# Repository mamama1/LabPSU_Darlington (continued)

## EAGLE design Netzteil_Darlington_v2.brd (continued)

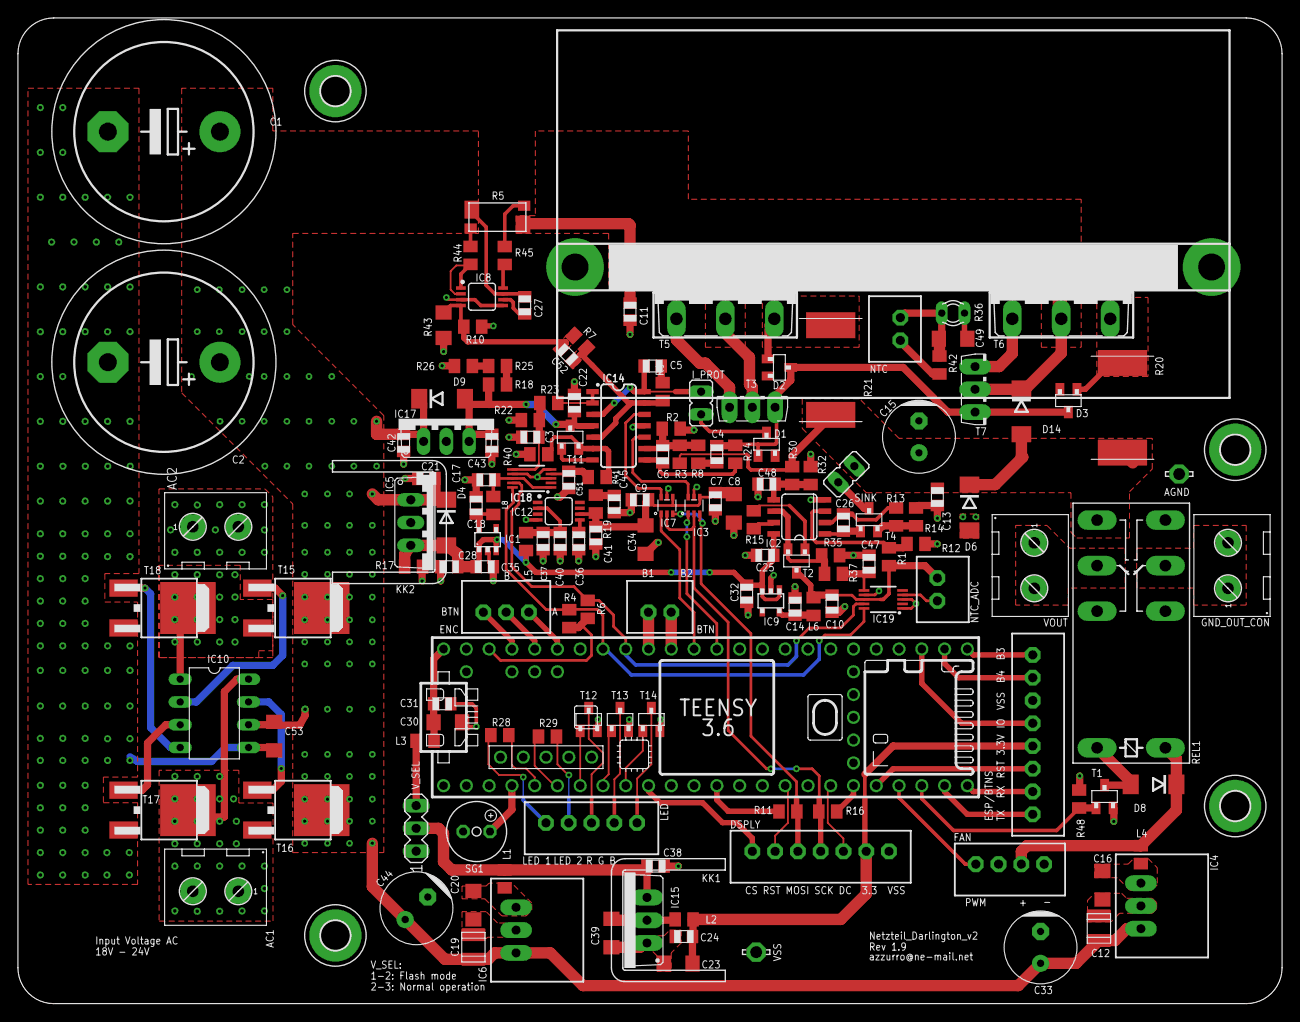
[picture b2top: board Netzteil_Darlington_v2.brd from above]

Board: 2 copper layers, 141.0 x 109.9 mm, 163 parts (0 on the bottom side), 109 nets.

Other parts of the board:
KK2: D01S
LED: JST-PH-2.0-5P
NTC: JST-PH-2.0-2P
NTC_ADC: JST-PH-2.0-2P
R15: 1k5 5% 1/8W; C0805K

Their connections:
3.3V_TH: NTC.2; also elsewhere on the board
unnamed 49: LED.3; also elsewhere on the board
unnamed 60: LED.1; also elsewhere on the board
unnamed 63: LED.2; also elsewhere on the board
unnamed 80: LED.4; also elsewhere on the board
unnamed 82: LED.5; also elsewhere on the board
TH0: NTC.1; also elsewhere on the board
TH0_ADC: NTC_ADC.1; also elsewhere on the board

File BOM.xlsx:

Qty | Value | Device | Package | Parts | Description | OC_MOUSER | OC_MOUSER_ADD | OC_MOUSER_ADD2
2 |  | JP1E | JP1 | I_PROT, SINK | JUMPER
3 |  | JST-PH-2.0-2P | JST-PH-2.0-2P | BTN, NTC, NTC_ADC | PIN HEADER
1 |  | JST-PH-2.0-3P | JST-PH-2.0-3P | ENC | PIN HEADER
1 |  | JST-PH-2.0-4P | JST-PH-2.0-4P | FAN | PIN HEADER
1 |  | JST-PH-2.0-5P | JST-PH-2.0-5P | LED | PIN HEADER
1 |  | JST-PH-2.0-7P | JST-PH-2.0-7P | DSPLY | PIN HEADER
1 |  | JST-PH-2.0-8P | JST-PH-2.0-8P | ESP/BTNS | PIN HEADER
1 |  | KL2691311500002 | KL2-691311500002 | VOUT | Printklemme 2-polig | 710-691311500002 | 565-72912-2 | 565-6883
1 |  | MA03-1 | MA03-1 | V_SEL | PIN HEADER
2 | 0R1 0.5% 7W | R-SMDSLN2 | SLN2 | R20, R21 | R | 66-SLN5TTED82L0D
1 | 1.27R 1% 1/10W | R-SMD0805 | C0805K | R19 | R | 71-CRCW08051R27FKEA
2 | 10.1k 0.1% 10ppm 1/10W | R-SMD0805 | C0805K | R22, R32 | R | 660-RN732ATTD1012B25
2 | 10000µ/50V | CPOL-USE10-22.5 | EB22,5D | C1, C2 | POLARIZED CAPACITOR, American symbol | 647-UVZ1H103MRD
2 | 100R 0.1% 5ppm 1/10W | R-SMD0805 | C0805K | R44, R45 | R | 756-PCF080513100RBT1
1 | 100k | NTC640 | P640 | R36 | PHILIPS NTC | 594-NTCLE213E3104HXB
1 | 100n opt/50V | CC/0805 | 805 | C13 | Kondensator | 810-C2012X7R2A104K
9 | 100n/16V | CC/0805 | 805 | C3, C7, C9, C10, C17, C24, C31, C38, C48 | Kondensator | 810-C2012X7R2A104K
5 | 100n/35V | CC/0805 | 805 | C22, C25, C28, C40, C43 | Kondensator | 810-C2012X7R2A104K
1 | 100n/50V | CC/0805 | 805 | C27 | Kondensator | 810-C2012X7R2A104K
3 | 100µ/50V | C+3.5/8 | C+/3.5/8 | C15, C33, C44 |  | 667-EEU-FR1H101
1 | 10R 0.5% 50 ppm 1/4W | R-SMD0805 | C0805K | R14 | R | 660-SG73G2ATTD10R0D
1 | 10k 0.1% 10ppm | R-SMD0805 | C0805K | R2 | R | 667-ERA-6ARW103V
4 | 10k 5% 1/10W | R-SMD0805 | C0805K | R4, R6, R7, R48 | R | 652-CR0805-JW-103ELF
1 | 10m 0.1% 15ppm 0.5W | R-CSM2512 | CSM2512 | R5 |  | 71-CSM25120R0100BST
2 | 10n/16V | CC/0805 | 805 | C47, C51 | Kondensator | 80-C0805C103K1R
1 | 10n/50V | CC/0805 | 805 | C4 | Kondensator | 80-C0805C103K1R
7 | 10µ/16V | CC/1206 | 1206 | C8, C20, C23, C30, C34, C39, C49 | Kondensator | 963-TMK316AB7106KL-T
1 | 10µ/25V | CC/1206 | 1206 | C16 | Kondensator | 963-TMK316AB7106KL-T
2 | 10µ/50V | CAPACITOR-1210 | C1210 | C12, C19 | Capacitors | 81-GRM32ER71H106MA2L
1 | 12k 0.5% 50 ppm 1/10W | R-SMD0805 | C0805K | R1 | R | 754-RR1220P-123D
1 | 1k 0.5% 50 ppm 1/10W | R-SMD0805 | C0805K | R13 | R | 754-RR1220P-102D
4 | 1k 1% 1/8W | R-SMD0805 | C0805K | R18, R24, R25, R26 | R | 652-CR0805FX-1001ELF
1 | 1k5 5% 1/8W | R-SMD0805 | C0805K | R15 | R | 652-CR0805FX-1501ELF
2 | 1n/50V | CC/0805 | 805 | C5, C26 | Kondensator | 603-CC805KRX7R0BB102
5 | 1µ/16V | CC/0805 | 805 | C14, C18, C36, C41, C45 | Kondensator | 963-UMK212B7105KG-T
3 | 1µ/35V | CC/0805 | 805 | C32, C35, C37 | Kondensator | 963-UMK212B7105KG-T
1 | 1µ/50V | CC/1206 | 1206 | C53 | Kondensator | 603-CC126KKX7R9BB105
2 | 2.2k 5% 1/10W | R-SMD0805 | C0805K | R37, R41 | R | 652-CR0805FX-2201ELF
2 | 220R 5% 1/10W | R-SMD0805 | C0805K | R28, R29 | R | 652-CR0805FX-2200ELF
1 | 221R 0.5% 50ppm 1/10W | R-SMD0805 | C0805K | R12 | R | 754-RR1220P-2210D-M
2 | 22R 5% 1/10W | R-SMD0805 | C0805K | R11, R16 | R | 652-CR0805JW-220ELF
1 | 22p opt/35V C0G | CC/0805 | 805 | C52 | Kondensator | 603-CC805JRNPO9BN220
1 | 22pF/35V C0G | CC/0805 | 805 | C6 | Kondensator | 603-CC805JRNPO9BN220
1 | 2k2 5% 1/8W | R-SMD0805 | C0805K | R17 | R | 652-CR0805JW-222ELF
1 | 30k 0.1% 10ppm | R-SMD0805 | C0805K | R3 | R | 667-ERA-6ARW303V
1 | 330n opt/50V | CC/0805 | 805 | C11 | Kondensator | 80-C0805C334K5RECTU
2 | 330n/50V | CC/0805 | 805 | C21, C42 | Kondensator | 80-C0805C334K5RECTU
1 | 4.7k 1% 1/10W | R-SMD0805 | C0805K | R9 | R | 652-CR0805FX-4701ELF
2 | 4.7k 5% 1/10W | R-SMD0805 | C0805K | R35, R40 | R | 652-CR0805FX-4701ELF
1 | 4.7k opt 1% 1/10W | R-SMD0805 | C0805K | R10 | R | 652-CR0805FX-4701ELF
1 | 47k 1% 1/10W | R-SMD0805 | C0805K | R8 | R | 652-CR0805FX-4702ELF
1 | 5k 0.1% 25ppm | R-EU_R1206 | R1206 | R43 | RESISTOR, European symbol | 71-TNPW12065K00BEEN
1 | 64.9k 1% 1/10W | R-SMD0805 | C0805K | R42 | R | 652-CR0805FX-6492ELF
1 | 7815TV | 7815TV | TO220V | IC5 | Positive VOLTAGE REGULATOR | 511-L7815CV-DG
1 | 7818TV | 7818TV | TO220V | IC17 | Positive VOLTAGE REGULATOR | 511-L7818CV-DG
2 | 90.9k 0.1% 10ppm 1/10W | R-SMD0805 | C0805K | R23, R30 | R | 279-RN73CA-90.9K
1 | AC1 | KL2691311500002 | KL2-691311500002 | AC1 | Printklemme 2-polig | 710-691311500002 | 693-8601.2001.08 | 693-3101.0010
1 | AC2 | KL2691311500002 | KL2-691311500002 | AC2 | Printklemme 2-polig | 710-691311500002 | 693-8601.2001.08
2 | ADS1115 | ADS1015 | MSOP10 | IC18, IC19 | ADS1015 12-BIT ADC | 595-ADS1115IDGSR
3 | BAT54FILMY | DBAT54FILMY | SOT23 | D1, D2, D3 |  | 511-BAT54FILMY
2 | BC847ALT1G | T-NPNSOT23-BEC | SOT23-BEC | T2, T11 | NPN Transistor | 863-BC847ALT1G
2 | BD139 | T-NPNTO126-ECB | TO126 | T3, T7 | NPN Transistor | 511-BD139-10
1 | BUZZER | BUZZER | 254-EMB73-RO | SG1 | BUZZER Source: Buerklin | 254-EMB73-RO
5 | CGRB307-G | DWIDE | DO214AA-CGRB307-G | D4, D6, D8, D9, D14 |  | 750-CGRB307-G
1 | D01S | D01S | D01S | KK1 | HEATSINK
2 | DAC8311 | DAC8X11 | SC-70-6 | IC3, IC7 |  | 595-DAC8311IDCKR
1 | G2R-2-DC12 | REL-2UG2R2 | REL-G2R2 | REL1 |  | 653-G2R-2-DC12
1 | GND | KL2691311500002 | KL2-691311500002 | GND_OUT_CON | Printklemme 2-polig | 710-691311500002
1 | HSOMNI-UNI-41-75 | HSOMNI-UNI-41-75 | OMNI-UNI-41-75 | HS2 |  | 567-OMNI-UNI-41-75 | 567-OMNI-UC | 567-CD-02-05-247
4 | IRFR7546TRPBF | T-NMOSNTD4963N | DPACK | T15, T16, T17, T18 | Transistor N-Channel MOSFET | 942-IRFR7546TRPBF
1 | LD33V | LD33V | TO220V | IC15 |  | 511-LD1117V33
2 | LSP13 | LSP13 | LSP13 | AGND, VSS | SOLDER PAD drill 1.3 mm, distributor Buerklin, 12H562
1 | LT4320DIL08 | LT4320DIL08 | DIL08 | IC10 |  | 584-LT4320HN8-1#PBF
1 | LTC6102HMS8#PBF | LTC6102 | MSOP8-0.65-3X3MM | IC8 |  | 584-LTC6102HMS8#PBF
4 | MOUNT-PAD-ROUND3.3 | MOUNT-PAD-ROUND3.3 | 3,3-PAD | H1, H2, H3, H4 | MOUNTING PAD, round
7 | MPZ2012S601AT000 | L0805 | C0805K | L1, L2, L3, L4, L5, L6, L8 | High Power Density, High Efficiency, Shielded Inductors | 810-MPZ2012S601AT000
2 | NCP718BSN330T1G | NCP718 | SOT23-5 | IC1, IC9 |  | 863-NCP718BSN330T1G
1 | OPA2197 | DUAL-OPVSOP8 | SOP8 | IC2 |  | 595-OPA2197IDR
5 | PMV130ENEAR | T-NMOSIRLML2502PBF | SOT23 | T1, T4, T12, T13, T14 | Transistor N-Channel MOSFET | 771-PMV130ENEAR
1 | QUAD-OPVOPA4197 | QUAD-OPVOPA4197 | SO14 | IC14 |  | 595-OPA4197IDR
1 | REF5040 | REF50XXVSSOP8 | MSOP8-0.65-3X3MM | IC12 |  | 595-REF5040AIDGKR
1 | TEENSY_3.5/3.6 | TEENSY_3.5/3.6 | TEENSY_3.5/3.6 | U$33 |  | 474-DEV-14055
2 | TIP3055 | T-NPNTOP3AV-BCE | TOP3AV | T5, T6 | NPN Transistor | 863-TIP3055G
1 | VXO78012-1000 | 78XX-DC-DC-UNI-VXO-OKI | 78XX-DC-DC | IC4 |  | 490-VXO7812-1000
1 | VXO7805-1000 | 78XX-DC-DC-UNI-VXO-OKI | 78XX-DC-DC | IC6 |  | 490-VXO7805-1000

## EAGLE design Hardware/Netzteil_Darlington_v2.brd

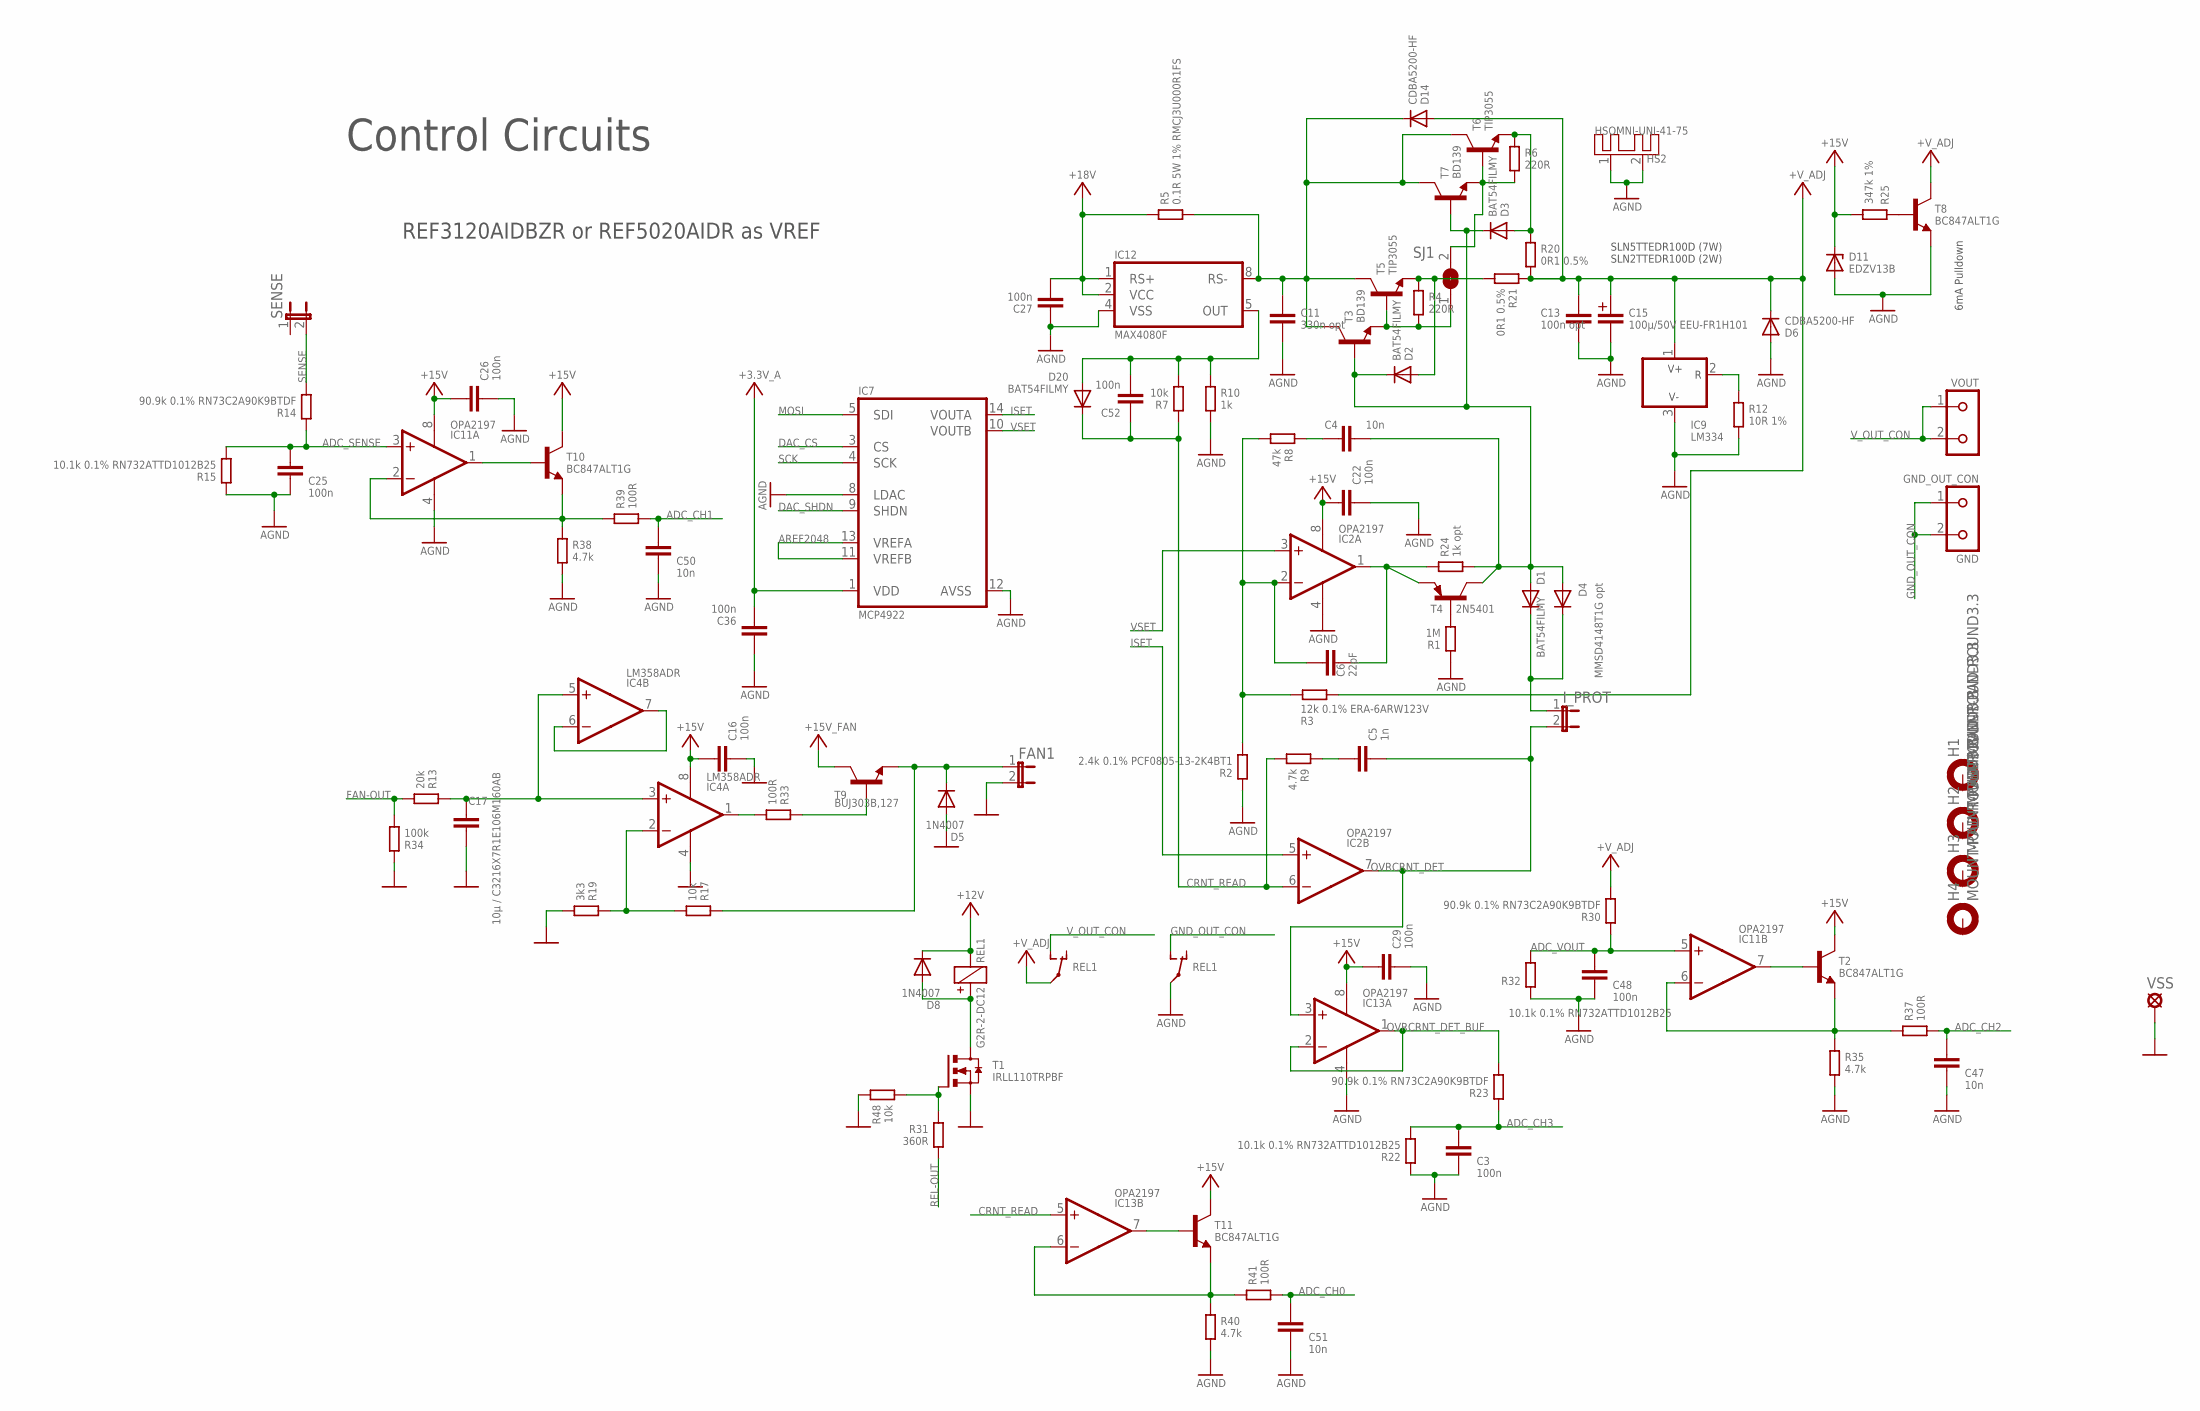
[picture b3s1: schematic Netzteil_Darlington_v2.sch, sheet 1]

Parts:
C3, C16, C22, C25, C26, C27, C29, C36, C48, C52: 100n; 0805
C4, C47, C50, C51: 10n; 0805
C5: 1n; 0805
C6: 22pF; 0805
C11: 330n opt; 0805
C13: 100n opt; 0805
C15: 100µ/50V EEU-FR1H101; C+/3.5/8
C17: 10µ / C3216X7R1E106M160AB; 1206
D1, D2, D3, D20: BAT54FILMY; SOT23
D4: MMSD4148T1G opt; SOD-123
D5, D8: 1N4007; DO214AA
D6, D14: CDBA5200-HF; DO214AC-2
D11: EDZV13B; SOD-523
FAN1: JP1E; JP1
GND_OUT_CON: GND; KL2-691311500002
H1, H2, H3, H4: MOUNT-PAD-ROUND3.3; 3,3-PAD
HS2: HSOMNI-UNI-41-75; OMNI-UNI-41-75
IC2, IC11, IC13: OPA2197; SOP8
IC4: LM358ADR; SOP8
IC7: MCP4922; TSSOP14
IC9: LM334; TO92-G
IC12: MAX4080F; SOP8
I_PROT: JP1E; JP1
R1: 1M; C0603K
R2: 2.4k 0.1% PCF0805-13-2K4BT1; C0805K
R3: 12k 0.1% ERA-6ARW123V; C0805K
R4, R6: 220R; C0805K
R5: 0.1R 5W 1% RMCJ3U000R1FS; RMC-J3
R7, R17, R48: 10k; C0805K
R8: 47k; C0805K
R9, R35, R38, R40: 4.7k; C0805K
R10: 1k; C0805K
R12: 10R 1%; C0805K
R13: 20k; C0805K
R14, R23, R30: 90.9k 0.1% RN73C2A90K9BTDF; C0805K
R15, R22, R32: 10.1k 0.1% RN732ATTD1012B25; C0805K
R19: 3k3; C0805K
R20, R21: 0R1 0.5%; SLN2
R24: 1k opt; C0805K
R25: 347k 1%; C0805K
R31: 360R; C0805K
R33, R37, R39, R41: 100R; C0805K
R34: 100k; C0805K
REL1: G2R-2-DC12; REL-G2R2
SENSE: JP1E; JP1
SJ1: SJ
T1: IRLL110TRPBF; SOT223-4
T2, T8, T10, T11: BC847ALT1G; SOT23-BEC
T3, T7: BD139; TO126
T4: 2N5401; TO92-G
T5, T6: TIP3055; TOP3AV
T9: BUJ303B,127; TO220V
VOUT: KL2691311500002; KL2-691311500002
VSS: LSP13

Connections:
+3.3V_A: C36.2, IC7.1 (VDD); also elsewhere on the board
+12V: D8.C, REL1.-; also elsewhere on the board
+15V: C16.1, C22.1, C26.1, C29.1, D11.C, IC2.8 (V+), IC4.8 (V+), IC11.8 (V+), IC13.8 (V+), R25.2, T2.C, T10.C, T11.C; also elsewhere on the board
+15V_FAN: T9.2 (C); also elsewhere on the board
+18V: C27.2, IC12.1 (RS+), IC12.2 (VCC), R5.1; also elsewhere on the board
+V_ADJ: C13.1, C15.+, D6.C, D14.A, IC9.1 (V+), R3.1, R20.2, R21.1, R30.2, REL1.P1, T8.C
ADC_CH0: C51.1, R41.2; also elsewhere on the board
ADC_CH1: C50.1, R39.2; also elsewhere on the board
ADC_CH2: C47.1, R37.2; also elsewhere on the board
ADC_CH3: C3.1, R22.2, R23.1; also elsewhere on the board
ADC_SENSE: C25.1, IC11.3 (+IN), R14.1, R15.2
ADC_VOUT: C48.1, IC11.5 (+IN), R30.1, R32.2
AGND: C3.2, C11.2, C13.2, C15.-, C22.2, C25.2, C26.2, C27.1, C29.2, C36.1, C47.2, C48.2, C50.2, C51.2, D6.A, D11.A, HS2.1, HS2.2, IC2.4 (V-), IC7.8 (LDAC), IC7.12 (AVSS), IC9.3 (V-), IC11.4 (V-), IC12.4 (VSS), IC13.4 (V-), R1.1, R2.1, R10.2, R12.2, R15.1, R22.1, R32.1, R35.2, R38.2, R40.2, REL1.P2, T8.E; also elsewhere on the board
AREF2048: IC7.11 (VREFB), IC7.13 (VREFA); also elsewhere on the board
CRNT_READ: C52.1, D20.3 (C), IC2.6 (-IN), IC13.5 (+IN), R7.1, R9.2
DAC_CS: IC7.3 (CS); also elsewhere on the board
DAC_SHDN: IC7.9 (SHDN); also elsewhere on the board
FAN-OUT: R13.2, R34.2; also elsewhere on the board
GND_OUT_CON: GND_OUT_CON.1, GND_OUT_CON.2, REL1.S2 (S)
ISET: IC2.5 (+IN), IC7.14 (VOUTA)
MOSI: IC7.5 (SDI); also elsewhere on the board
unnamed: C11.1, D14.C, IC12.8 (RS-), R5.2, T3.2 (C), T5.C, T6.C, T7.2 (C)
unnamed: D3.1 (A), R6.1, R20.1, T6.E
unnamed: R6.2, SJ1.2, T6.B, T7.1 (E)
unnamed: C6.1, IC2.2 (-IN), R2.2, R3.2, R8.2
unnamed: C52.2, D20.1 (A), IC12.5 (OUT), R7.2, R10.1
unnamed: D2.1 (A), R4.1, R21.2, T5.E
unnamed: D1.3 (C), D4.C, I_PROT.1
unnamed: R25.1, T8.B
unnamed: D8.A, REL1.+, T1.2 (D), T1.4 (D)
unnamed: R4.2, SJ1.1, T3.1 (E), T5.B
unnamed: IC9.2 (R), R12.1
unnamed: IC4.6 (-IN), IC4.7 (OUT)
unnamed: R1.2, T4.2 (B)
unnamed: C6.2, IC2.1 (OUT), R24.1, T4.1 (E)
unnamed: C4.2, D1.1 (A), D2.3 (C), D3.3 (C), D4.A, R24.2, T3.3 (B), T4.3 (C), T7.3 (B)
unnamed: C4.1, R8.1
unnamed: C5.1, R9.1
unnamed: C17.2, IC4.3 (+IN), IC4.5 (+IN), R13.1
unnamed: D5.C, FAN1.1, R17.1, T9.3 (E)
unnamed: IC4.2 (-IN), R17.2, R19.1
unnamed: R33.1, T9.1 (B)
unnamed: IC4.1 (OUT), R33.2
unnamed: R31.1, R48.2, T1.1 (G)
unnamed: IC11.7 (OUT), T2.B
unnamed: IC11.6 (-IN), R35.1, R37.1, T2.E
unnamed: IC11.1 (OUT), T10.B
unnamed: IC11.2 (-IN), R38.1, R39.1, T10.E
unnamed: IC13.7 (OUT), T11.B
unnamed: IC13.6 (-IN), R40.1, R41.1, T11.E
OVRCRNT_DET: C5.2, IC2.7 (OUT), IC13.3 (+IN), I_PROT.2
OVRCRNT_DET_BUF: IC13.1 (OUT), IC13.2 (-IN), R23.2
REL-OUT: R31.2; also elsewhere on the board
SCK: IC7.4 (SCK); also elsewhere on the board
SENSE: R14.2, SENSE.2
VSET: IC2.3 (+IN), IC7.10 (VOUTB)
VSS: C16.2, C17.1, D5.A, FAN1.2, IC4.4 (V-), R19.2, R34.1, R48.1, T1.3 (S), VSS.MP; also elsewhere on the board
V_OUT_CON: REL1.S1 (S), VOUT.1, VOUT.2

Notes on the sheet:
Control Circuits
6mA Pulldown
SLN5TTEDR100D (7W) SLN2TTEDR100D (2W)
REF3120AIDBZR or REF5020AIDR as VREF

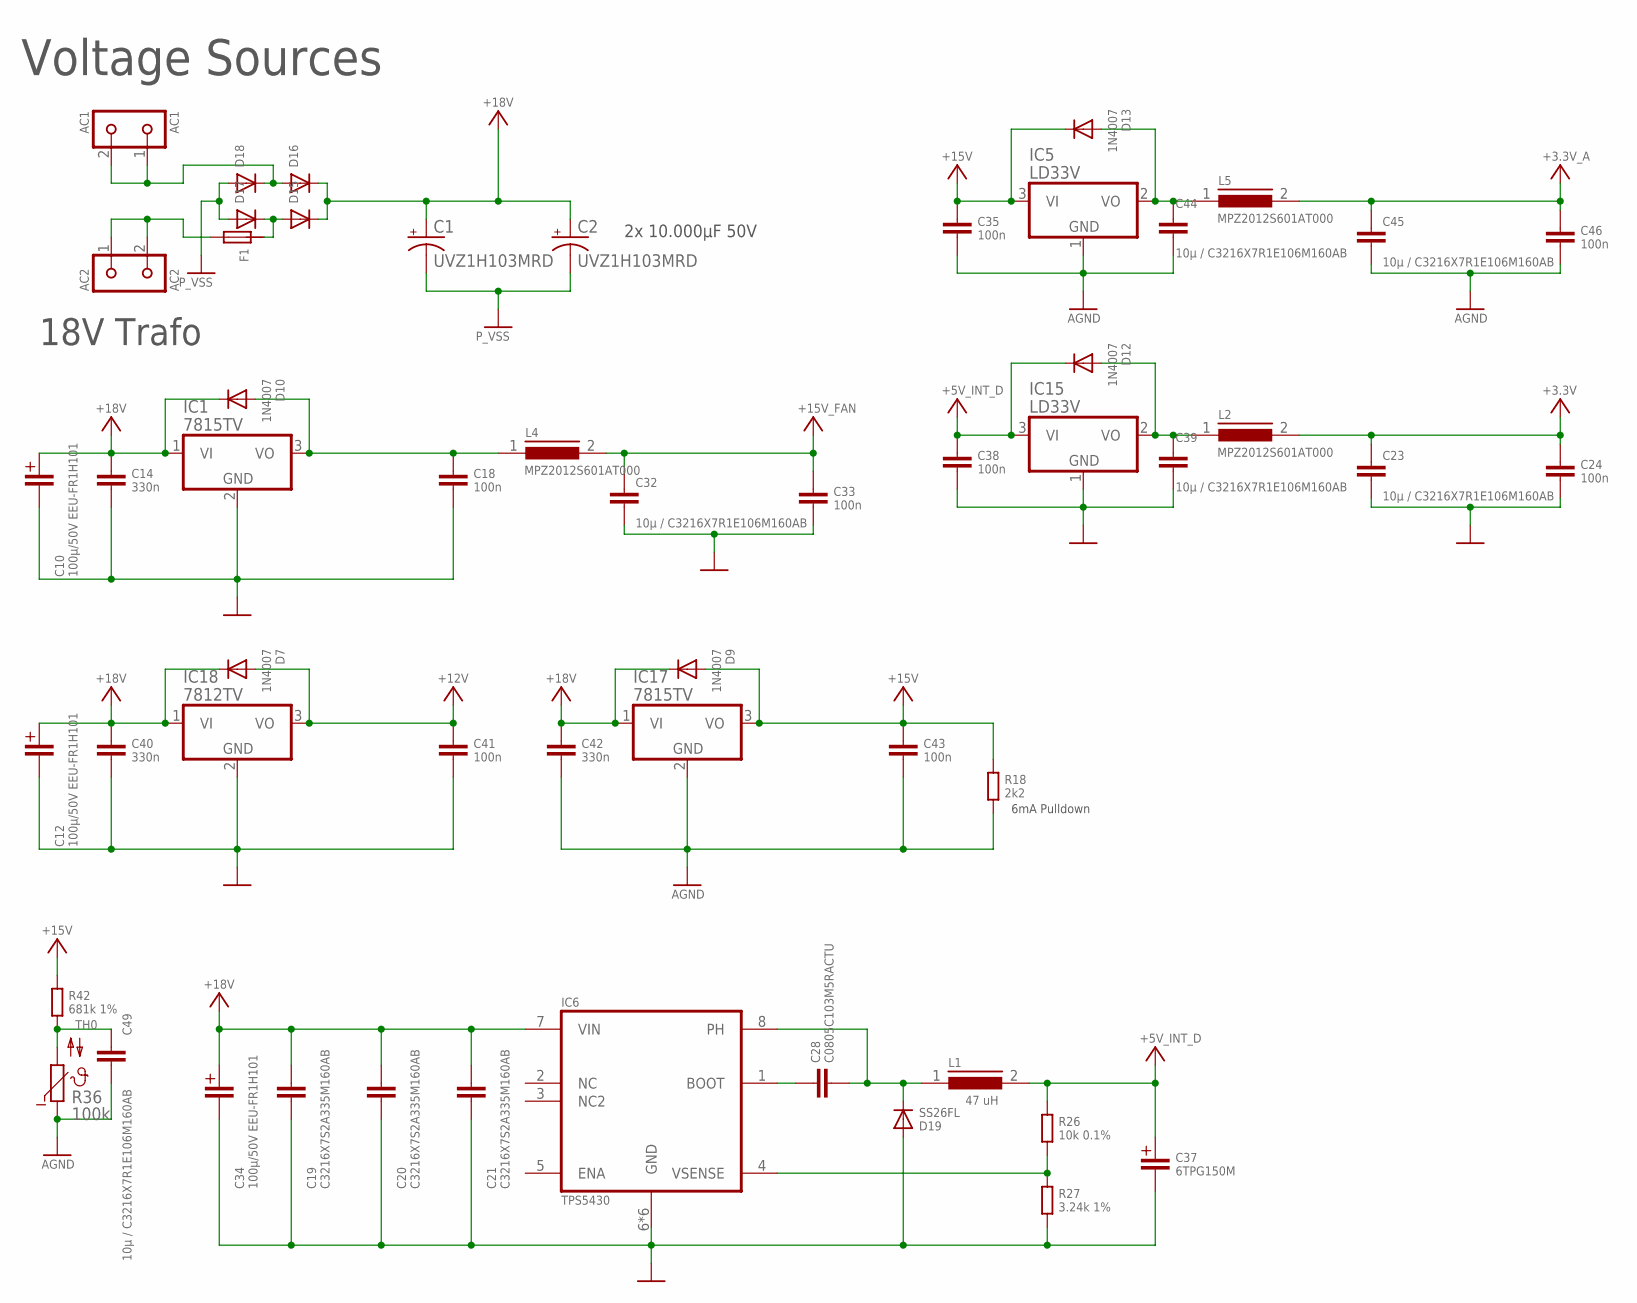
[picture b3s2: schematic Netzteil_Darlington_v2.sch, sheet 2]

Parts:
AC1: AC1; KL2-691311500002
AC2: AC2; KL2-691311500002
C1, C2: UVZ1H103MRD; EB22,5D
C10, C12, C34: 100µ/50V EEU-FR1H101; C+/3.5/8
C14, C40, C42: 330n; 0805
C18, C24, C33, C35, C38, C41, C43, C46: 100n; 0805
C19, C20, C21: C3216X7S2A335M160AB; 1206
C23, C32, C39, C44, C45, C49: 10µ / C3216X7R1E106M160AB; 1206
C28: C0805C103M5RACTU; 0805
C37: 6TPG150M; CT1210
D7, D9, D10, D12, D13: 1N4007; DO214AA
D15, D16, D17, D18: DTO263-PWR; TO-263AB-PWR
D19: SS26FL; SOD-123
F1: F5X20
IC1, IC17: 7815TV; TO220V
IC5, IC15: LD33V; TO220V
IC6: TPS5430; SOIC8POWERPAD
IC18: 7812TV; TO220V
L1: 47 uH; WE-PD
L2, L4, L5: MPZ2012S601AT000; C0805K
R18: 2k2; C0805K
R26: 10k 0.1%; C0805K
R27: 3.24k 1%; C0805K
R36: 100k; P640
R42: 681k 1%; C0603K

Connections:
+3.3V: C23.1, C24.1, L2.2; also elsewhere on the board
+3.3V_A: C45.1, C46.1, L5.2; also elsewhere on the board
+5V_INT_D: C37.+, C38.1, D12.C, IC15.3 (VI), L1.2, R26.1; also elsewhere on the board
+12V: C41.1, D7.A, IC18.3 (VO); also elsewhere on the board
+15V: C35.1, C43.1, D9.A, D13.C, IC5.3 (VI), IC17.3 (VO), R18.1, R42.1; also elsewhere on the board
+15V_FAN: C32.1, C33.1, L4.2; also elsewhere on the board
+18V: C1.+, C2.+, C10.+, C12.+, C14.1, C19.1, C20.1, C21.1, C34.+, C40.1, C42.1, D7.C, D9.C, D10.C, D15.2 (C), D15.2_PWR1 (C), D15.2_PWR2 (C), D15.2_PWR3 (C), D15.2_PWR4 (C), D15.2_PWR5 (C), D15.2_PWR6 (C), D15.2_PWR7 (C), D15.2_PWR8 (C), D15.2_PWR9 (C), D15.2_PWR10 (C), D15.2_PWR11 (C), D15.2_PWR12 (C), D16.2 (C), D16.2_PWR1 (C), D16.2_PWR2 (C), D16.2_PWR3 (C), D16.2_PWR4 (C), D16.2_PWR5 (C), D16.2_PWR6 (C), D16.2_PWR7 (C), D16.2_PWR8 (C), D16.2_PWR9 (C), D16.2_PWR10 (C), D16.2_PWR11 (C), D16.2_PWR12 (C), IC1.1 (VI), IC6.7 (VIN), IC17.1 (VI), IC18.1 (VI); also elsewhere on the board
AGND: C35.2, C42.2, C43.2, C44.1, C45.2, C46.2, C49.1, IC5.1 (GND), IC17.2 (GND), R18.2, R36.1; also elsewhere on the board
unnamed: C28.1, IC6.1 (BOOT)
unnamed: AC2.1, AC2.2, F1.3 (2), F1.4 (2)
unnamed: C28.2, D19.- (C), IC6.8 (PH), L1.1
unnamed: AC1.1, AC1.2, D16.1 (A), D16.3 (A), D18.2 (C), D18.2_PWR1 (C), D18.2_PWR2 (C), D18.2_PWR3 (C), D18.2_PWR4 (C), D18.2_PWR5 (C), D18.2_PWR6 (C), D18.2_PWR7 (C), D18.2_PWR8 (C), D18.2_PWR9 (C), D18.2_PWR10 (C), D18.2_PWR11 (C), D18.2_PWR12 (C)
unnamed: IC6.4 (VSENSE), R26.2, R27.1
unnamed: D15.1 (A), D15.3 (A), D17.2 (C), D17.2_PWR1 (C), D17.2_PWR2 (C), D17.2_PWR3 (C), D17.2_PWR4 (C), D17.2_PWR5 (C), D17.2_PWR6 (C), D17.2_PWR7 (C), D17.2_PWR8 (C), D17.2_PWR9 (C), D17.2_PWR10 (C), D17.2_PWR11 (C), D17.2_PWR12 (C), F1.1, F1.2 (1)
unnamed: C39.2, D12.A, IC15.2 (VO), L2.1
unnamed: C18.1, D10.A, IC1.3 (VO), L4.1
unnamed: C44.2, D13.A, IC5.2 (VO), L5.1
P_VSS: C1.-, C2.-, D17.1 (A), D17.3 (A), D18.1 (A), D18.3 (A)
TH0: C49.2, R36.2, R42.2; also elsewhere on the board
VSS: C10.-, C12.-, C14.2, C18.2, C19.2, C20.2, C21.2, C23.2, C24.2, C32.2, C33.2, C34.-, C37.-, C38.2, C39.1, C40.2, C41.2, D19.+ (A), IC1.2 (GND), IC6.6 (GND), IC6.POWERPAD (GND), IC6.PP1 (GND), IC6.PP2 (GND), IC6.PP3 (GND), IC6.PP4 (GND), IC15.1 (GND), IC18.2 (GND), R27.2; also elsewhere on the board

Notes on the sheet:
2x 10.000µF 50V
Voltage Sources
18V Trafo
6mA Pulldown

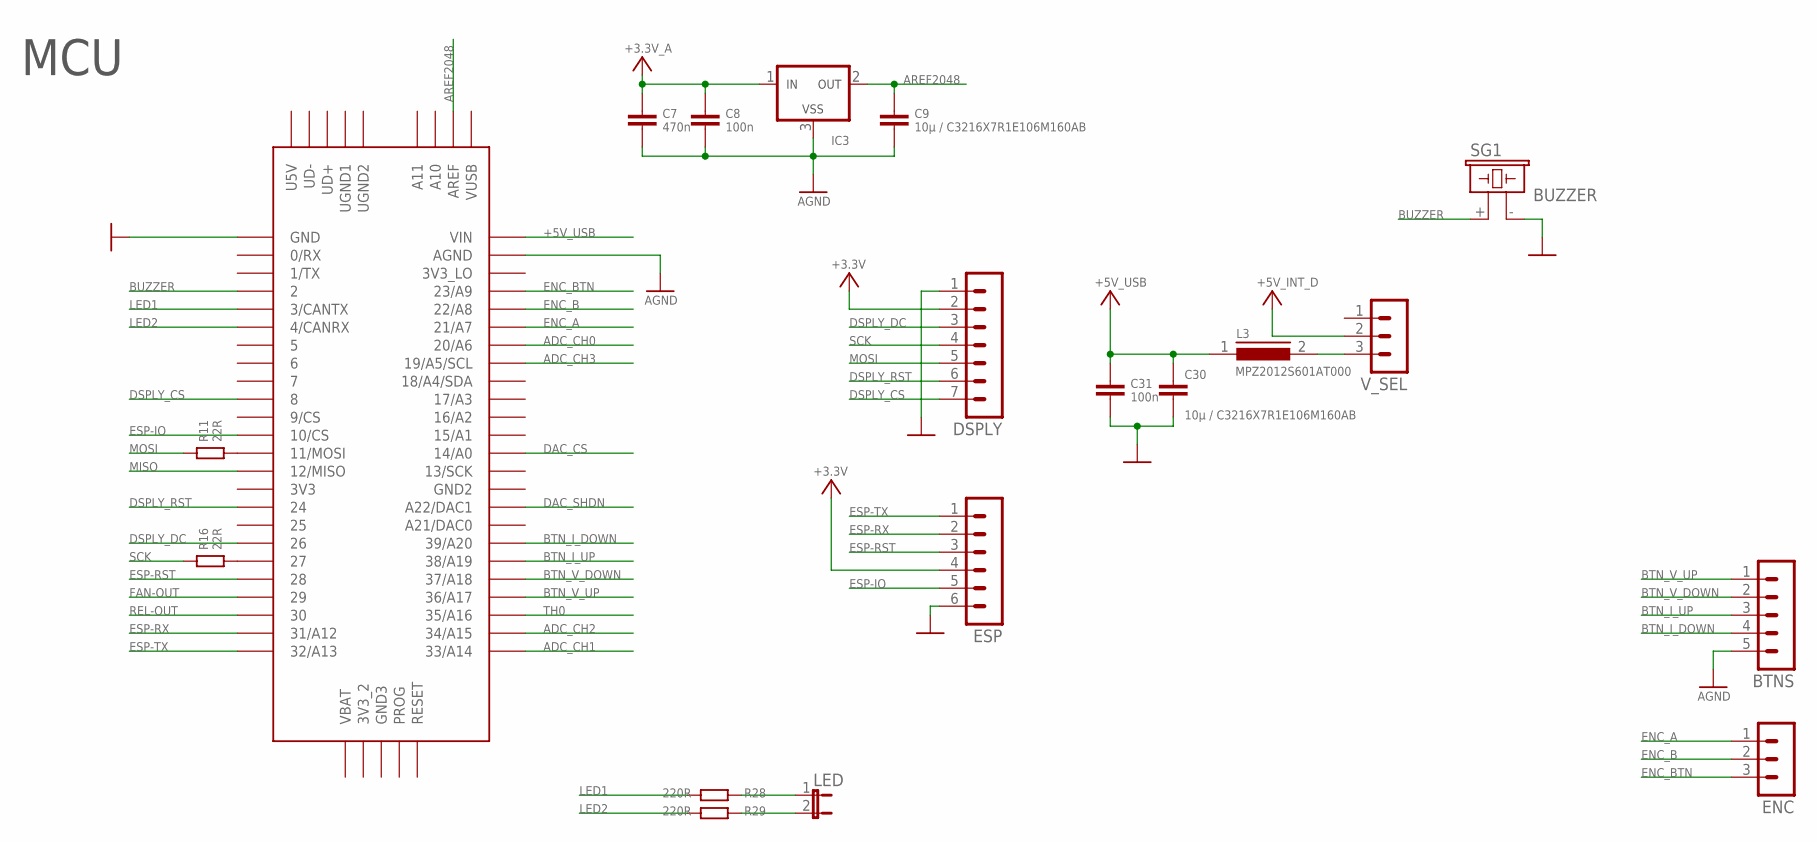
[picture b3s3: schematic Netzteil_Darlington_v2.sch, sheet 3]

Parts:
BTNS: MA05-1
C7: 470n; 0805
C8, C31: 100n; 0805
C9, C30: 10µ / C3216X7R1E106M160AB; 1206
DSPLY: MA07-1
ENC: MA03-1
ESP: MA06-1
IC3: REF3120; SOT23
L3: MPZ2012S601AT000; C0805K
LED: JP1E; JP1
R11, R16: 22R; C0805K
R28, R29: 220R; C0805K
SG1: BUZZER; 254-EMB73-RO
U$33: TEENSY_3.5/3.6
V_SEL: MA03-1

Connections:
+3.3V: DSPLY.2, ESP.4; also elsewhere on the board
+3.3V_A: C7.1, C8.1, IC3.1 (IN); also elsewhere on the board
+5V_INT_D: V_SEL.2; also elsewhere on the board
+5V_USB: C30.1, C31.1, L3.1, U$33.VIN
ADC_CH0: U$33.20/A6; also elsewhere on the board
ADC_CH1: U$33.33/A14; also elsewhere on the board
ADC_CH2: U$33.34/A15; also elsewhere on the board
ADC_CH3: U$33.19/A5/SCL; also elsewhere on the board
AGND: BTNS.5, C7.2, C8.2, C9.2, IC3.3 (VSS), U$33.AGND; also elsewhere on the board
AREF2048: C9.1, IC3.2 (OUT), U$33.AREF; also elsewhere on the board
BTN_I_DOWN: BTNS.4, U$33.39/A20
BTN_I_UP: BTNS.3, U$33.38/A19
BTN_V_DOWN: BTNS.2, U$33.37/A18
BTN_V_UP: BTNS.1, U$33.36/A17
BUZZER: SG1.+ (1), U$33.2
DAC_CS: U$33.14/A0; also elsewhere on the board
DAC_SHDN: U$33.A22/DAC1; also elsewhere on the board
DSPLY_CS: DSPLY.7, U$33.8
DSPLY_DC: DSPLY.3, U$33.26
DSPLY_RST: DSPLY.6, U$33.24
ENC_A: ENC.1, U$33.21/A7
ENC_B: ENC.2, U$33.22/A8
ENC_BTN: ENC.3, U$33.23/A9
ESP-IO: ESP.5, U$33.10/CS
ESP-RST: ESP.3, U$33.28
ESP-RX: ESP.2, U$33.31/A12
ESP-TX: ESP.1, U$33.32/A13
FAN-OUT: U$33.29; also elsewhere on the board
LED1: R28.1, U$33.3/CANTX
LED2: R29.1, U$33.4/CANRX
MISO: U$33.12/MISO
MOSI: DSPLY.5, R11.1; also elsewhere on the board
unnamed: R16.2, U$33.27
unnamed: R11.2, U$33.11/MOSI
unnamed: LED.1, R28.2
unnamed: LED.2, R29.2
unnamed: L3.2, V_SEL.3
REL-OUT: U$33.30; also elsewhere on the board
SCK: DSPLY.4, R16.1; also elsewhere on the board
TH0: U$33.35/A16; also elsewhere on the board
VSS: C30.2, C31.2, DSPLY.1, ESP.6, SG1.- (2), U$33.GND; also elsewhere on the board

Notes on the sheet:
MCU

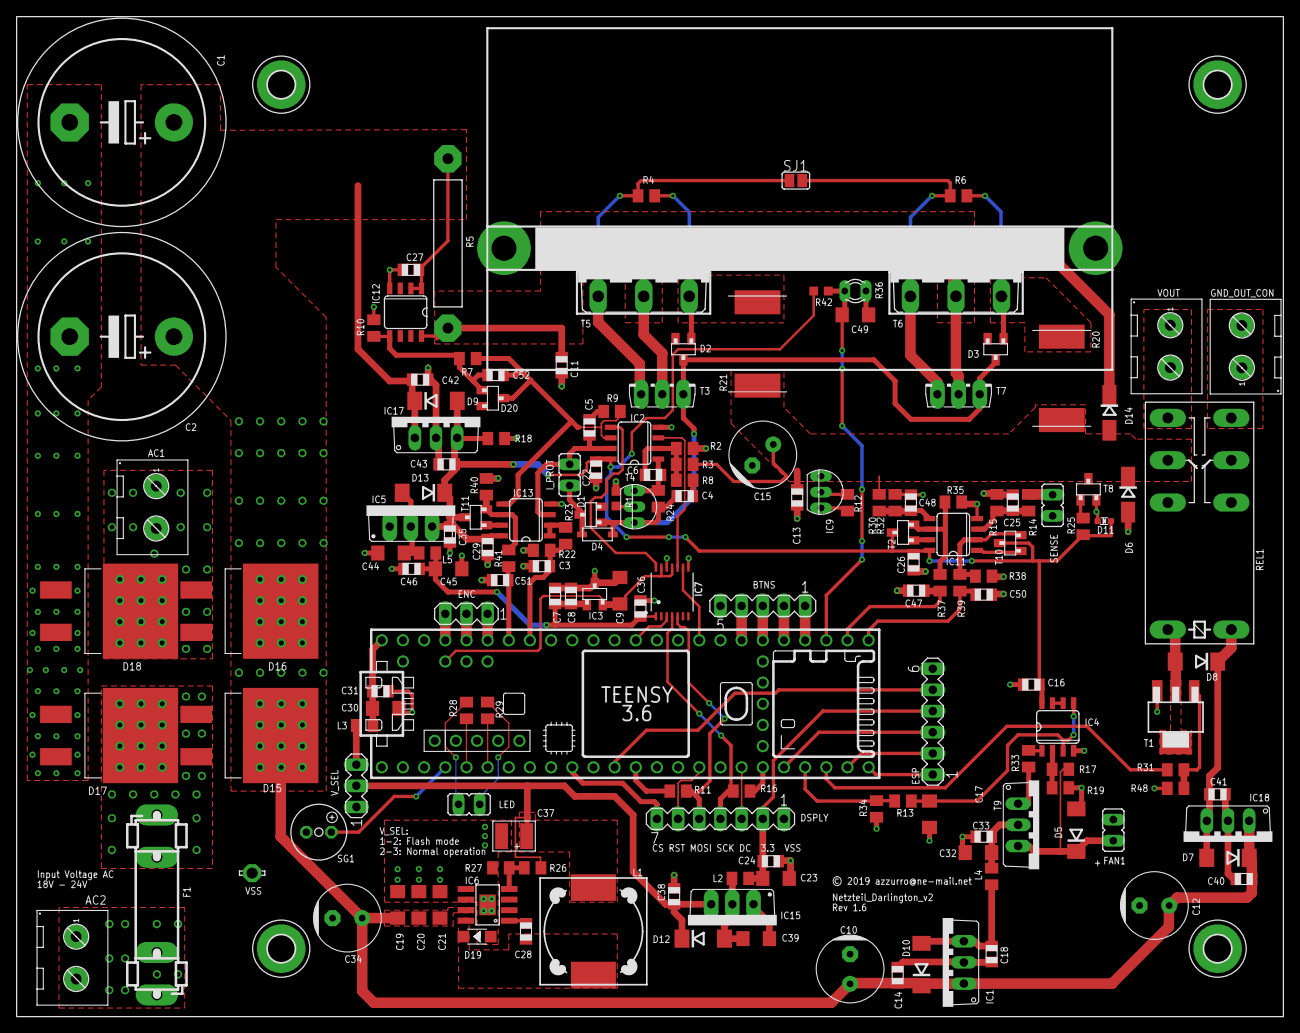
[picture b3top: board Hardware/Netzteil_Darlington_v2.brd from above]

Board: 2 copper layers, 152.0 x 120.0 mm, 169 parts (0 on the bottom side), 94 nets.

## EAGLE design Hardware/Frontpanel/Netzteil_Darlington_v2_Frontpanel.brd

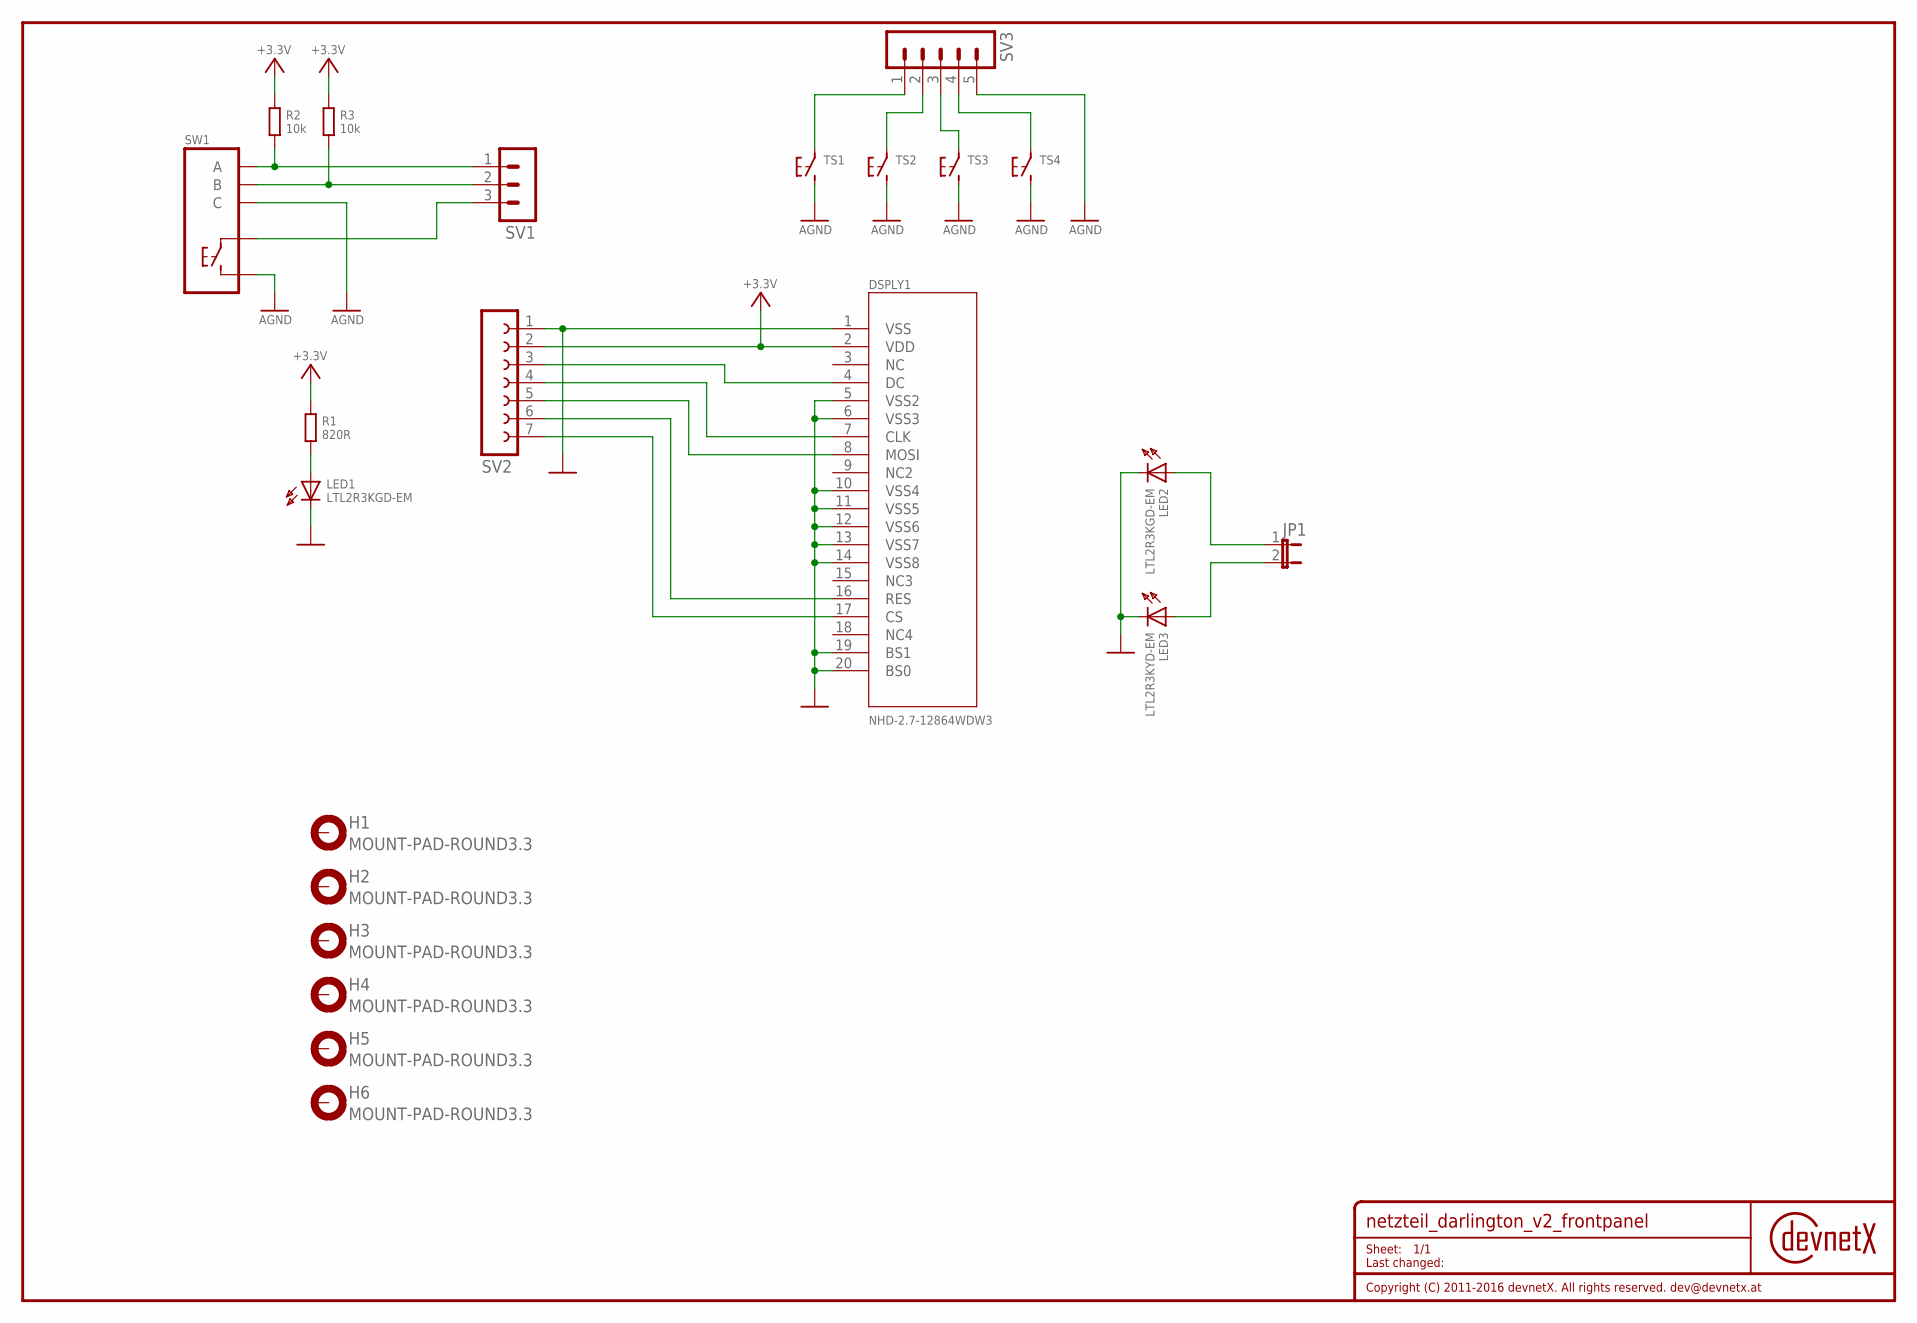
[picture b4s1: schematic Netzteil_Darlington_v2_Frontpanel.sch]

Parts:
DNX-NAME-1: DOC-R1.27; DRAWINGNAME-1.27
DSPLY1: NHD-2.7-12864WDW3
H1, H2, H3, H4, H5, H6: MOUNT-PAD-ROUND3.3; 3,3-PAD
JP1: JP1E; JP1
LED1, LED2: LTL2R3KGD-EM; LED5MM
LED3: LTL2R3KYD-EM; LED5MM
R1: 820R; C0805K
R2, R3: 10k; C0805K
SV1: MA03-1
SV2: FE07-1; FE07
SV3: MA05-1
SW1: EC12E-SW
TS1, TS2, TS3, TS4: TS1B3F-10XX; B3F-10XX

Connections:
+3.3V: DSPLY1.2 (VDD), R1.1, R2.1, R3.1, SV2.2
AGND: SV3.5, SW1.2, SW1.C, TS1.3 (2), TS2.3 (2), TS3.3 (2), TS4.3 (2)
unnamed: JP1.1, LED2.A
unnamed: JP1.2, LED3.A
unnamed: DSPLY1.4 (DC), SV2.3
unnamed: SV3.1, TS1.1
unnamed: R2.2, SV1.1, SW1.A
unnamed: DSPLY1.7 (CLK), SV2.4
unnamed: DSPLY1.8 (MOSI), SV2.5
unnamed: R3.2, SV1.2, SW1.B
unnamed: SV1.3, SW1.1
unnamed: SV3.2, TS2.1
unnamed: SV3.3, TS3.1
unnamed: SV3.4, TS4.1
unnamed: DSPLY1.16 (RES), SV2.6
unnamed: DSPLY1.17 (CS), SV2.7
unnamed: LED1.A, R1.2
VSS: DSPLY1.1 (VSS), DSPLY1.5 (VSS2), DSPLY1.6 (VSS3), DSPLY1.10 (VSS4), DSPLY1.11 (VSS5), DSPLY1.12 (VSS6), DSPLY1.13 (VSS7), DSPLY1.14 (VSS8), DSPLY1.19 (BS1), DSPLY1.20 (BS0), LED1.C, LED2.C, LED3.C, SV2.1
